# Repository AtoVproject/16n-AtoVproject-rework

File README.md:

<h1>16n AtoVproject Rework</h1>

Product page: https://atovproject.de/products/16nrework

Manual: https://atovproject.de/manuals/16nrework

This is an hardware modified version of the original 16n. https://github.com/16n-faderbank/16n

Fully assembled unit with high end aluminium enclosure, high end faders and set of cables available @ https://schneidersladen.de/de/atovproject-16n-atovproject-rework

Bourns compatible PCBs Panels and cases are available @ https://pushermanproductions.com/product/16n-euro-version-pcb-and-anodized-aluminium-black-panel/

BOM in the PCB folder

Please download the firmware from the original project https://github.com/16n-faderbank/16n/wiki/Firmware:-installation-instructions

<h2>The concept</h2>

The 16n Faderbank is aimed a solving a problem very specific to modular synthesis. As a patch is getting more and more complex a forest of cables has grown over your system before you know it. The 16n allows you to take the control from the modular into a very ergonomic controller that integrates perfectly into a modern studio.

The 16n is a faderbank sending CV, I2C, MIDI jack compatible with all standards, USB MIDI (compatible PC, Mac, iPad etc...) , making it the absolute ultimate controller for any of your hardware and software all in one! 

This unit was redesigned for a DIY workshop organised in the Berlin Modular community. The redesign was done following the wishes and desires of the community. The 16n AtoVproject redesign is the result of this initiative. 

https://www.youtube.com/watch?v=edriUxDgTsg

<h2>Modifications compared to the original are :</h2>

-Updated power section
  Isolated USB power supply. Proper voltage reference. Upgraded filtering.
    This greatly reduce the noise on the outputs. (Measured at less than 6mV)

-Selectable 5v or 10V outputs: Each can be configured to output either 10V or 5V using a dip switch on the back of the module (even when using 5V USB power supply)

-Outputs facing upwards: The outputs will be directly on the front panel reducing the footprint and making outputs much more accessible.

-Eurorack compatible: You would be able to mount the 16n as a 50hp module in your rack and power it from your own power supply. (+12V=42mA, -12V=0mA)

-The footprint of the jack is compatible for banana connectors! So you'll be able to use it with your Serge or Buchla system.

-I2C connector on the PCB to simplify connection to modules like the ER301

-Two versions of the board are available one with high quality ALPS faders and another one with Bourns mid range faders (1/3 of the price of the ALPS).

<h2>Credits</h2>

Based on original open source work by Brian Crabtree, Sean Hellfritsch, Tom Armitage and Brendon Cassidy. Circuit design update by AtoVproject aka Arthur Gibert

As stated by the original designers the original 16n folows a CC-BY-SA licence therefore the 16n AtoVproject is and will always remain entirely open source following the same licence.

If you are making modification to this design, you must correctly credit everyone involved in the initial version, and also share your own changes with the similar license. So you can’t make a fork of 16n or the 16n AtoVproject redesign that you don’t open-source yourself.

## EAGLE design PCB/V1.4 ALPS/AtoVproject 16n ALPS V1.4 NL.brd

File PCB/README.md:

<h1>Gerbers and eagle design files</h1>

Two versions of the board are available. One for high end ALPS faders (which are expensive and quite often out of stock) and another for lower cost Brouns faders (1/3 of the price and more readily available)

The PCB available at https://pushermanproductions.com/product/16n-euro-version-pcb-and-anodized-aluminium-black-panel/ is compatible only with the Brouns faders. 

<h2>Mouser Carts :</h2>

These are complete carts to have all the parts to make the build. They are valid for the latest revision of the boards (v1.4)
Resistors and capacitors are very small so I stronly recommand ordering more (little tip: order resistors and capacitors amounts to the next price break this will make you save a few cents)

Bourns Version
https://www.mouser.com/ProjectManager/ProjectDetail.aspx?AccessID=e279897c7f

ALPS Version
https://www.mouser.com/ProjectManager/ProjectDetail.aspx?AccessID=69297ae739

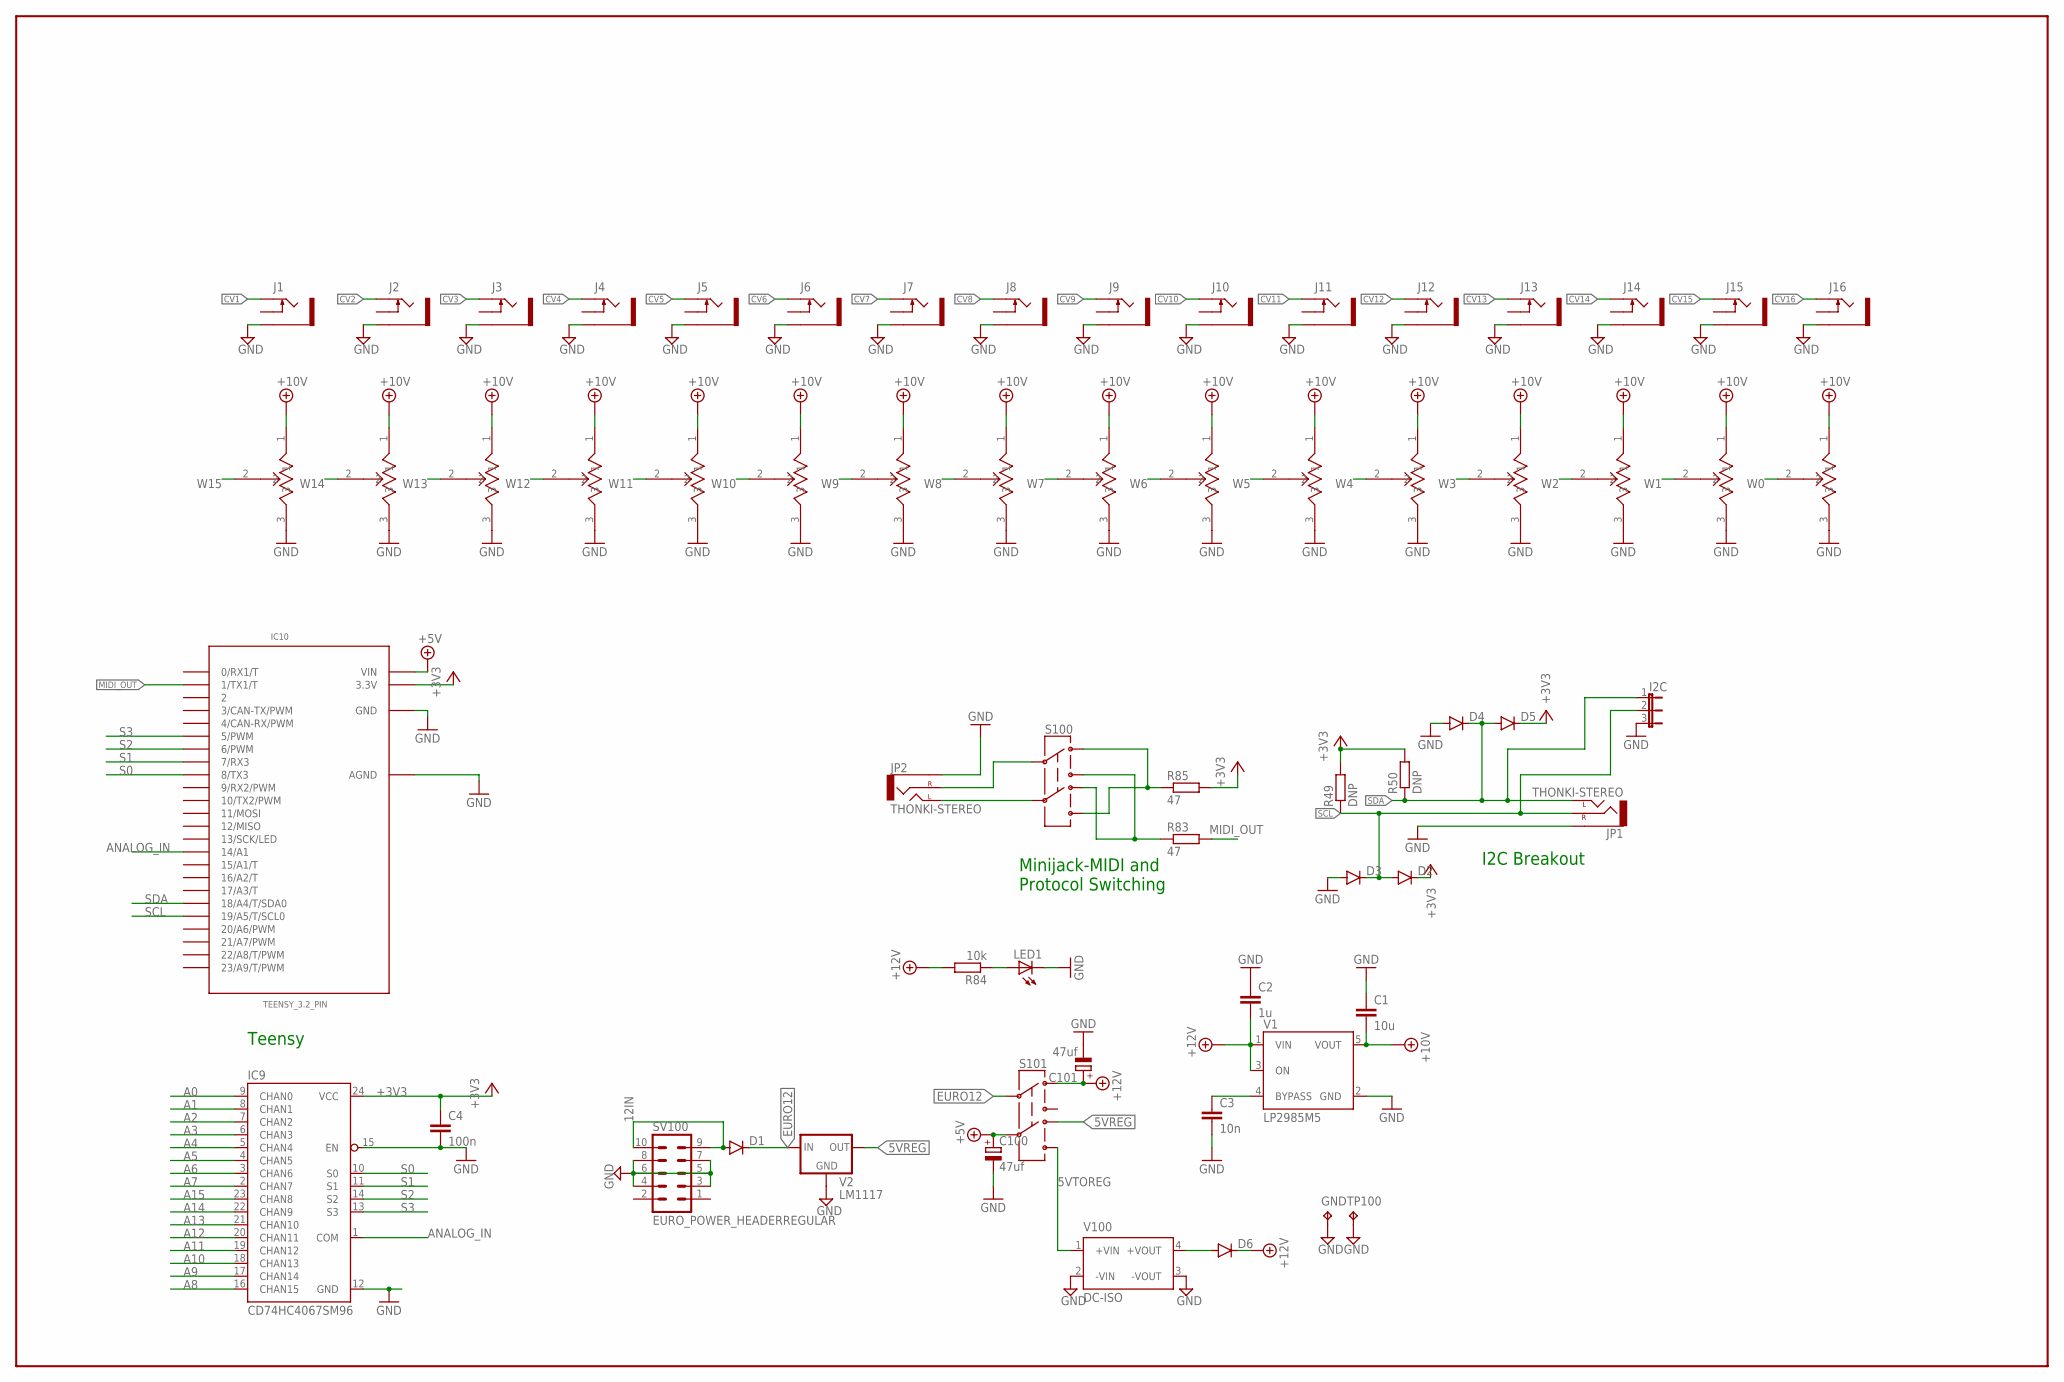
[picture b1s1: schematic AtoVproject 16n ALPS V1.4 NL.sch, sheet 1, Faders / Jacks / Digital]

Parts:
C1: 10u; C0805
C2: 1u; C0805
C3: 10n; C0805
C4: 100n; C0805
C100, C101: 47uf; E2,5-6
D1, D6: DIODE-SOD123; SOD123
D2, D3, D4, D5: DIODESOD123; SOD-123
GND: TPPAD1-17; P1-17
I2C: JP2E; JP2
IC9: CD74HC4067SM96; SOIC127P1030X265-24
IC10: TEENSY_3.2_PIN; TEENSY_3_AND_LC_SERIES_BOARDS_V1.4_TEENSY_3.0-3.2&LC_DIL
J1, J2, J3, J4, J5, J6, J7, J8, J9, J10, J11, J12, J13, J14, J15, J16: THONKICONN; WQP-PJ301M-12JACK-BANANA
JP1, JP2: THONKI-STEREO; WQP-PJ366ST_JACK
LED1: LED; LED3MM
R49, R50: DNP; R0805
R83, R85: 47; R0805
R84: 10k; R0805
S100, S101: SWITCH-DPDTEG2211; EG2211
SV100: EURO_POWER_HEADERREGULAR; EURO_POWER_HEADER
TP100: TPPAD1-17; P1-17
U$1, U$2, U$3, U$4, U$5, U$6, U$7, U$8, U$9, U$10, U$11, U$12, U$13, U$14, U$15, U$16: SLIDERSALPS-60MM; MONOME_RS6011SP600
V1: LP2985M5; SOT23-5
V2: LM1117; SOT223
V100: DC-ISO; TMA

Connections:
5VREG: S101.P2-TA (4), V2.OUT, V2.TAB (OUT)
5VTOREG: S101.P2-TB (6), V100.1 (+VIN)
12IN: D1.A, SV100.9, SV100.10
+3V3: C4.1, D2.C, D5.C, IC9.24 (VCC), IC10.3.3V, R49.2, R50.2, R85.2
+5V: C100.+, IC10.VIN, S101.P2 (5); also elsewhere on the board
+10V: C1.2, U$1.1, U$2.1, U$3.1, U$4.1, U$5.1, U$6.1, U$7.1, U$8.1, U$9.1, U$10.1, U$11.1, U$12.1, U$13.1, U$14.1, U$15.1, U$16.1, V1.5 (VOUT)
+12V: C2.2, C101.+, D6.C, R84.2, S101.P1-TA (1), V1.1 (VIN), V1.3 (ON); also elsewhere on the board
A0: IC9.9 (CHAN0); also elsewhere on the board
A1: IC9.8 (CHAN1); also elsewhere on the board
A2: IC9.7 (CHAN2); also elsewhere on the board
A3: IC9.6 (CHAN3); also elsewhere on the board
A4: IC9.5 (CHAN4); also elsewhere on the board
A5: IC9.4 (CHAN5); also elsewhere on the board
A6: IC9.3 (CHAN6); also elsewhere on the board
A7: IC9.2 (CHAN7); also elsewhere on the board
A8: IC9.16 (CHAN15); also elsewhere on the board
A9: IC9.17 (CHAN14); also elsewhere on the board
A10: IC9.18 (CHAN13); also elsewhere on the board
A11: IC9.19 (CHAN12); also elsewhere on the board
A12: IC9.20 (CHAN11); also elsewhere on the board
A13: IC9.21 (CHAN10); also elsewhere on the board
A14: IC9.22 (CHAN9); also elsewhere on the board
A15: IC9.23 (CHAN8); also elsewhere on the board
ANALOG_IN: IC9.1 (COM), IC10.14/A0 (14/A1)
CV1: J1.P$1_TIP (TIP); also elsewhere on the board
CV2: J2.P$1_TIP (TIP); also elsewhere on the board
CV3: J3.P$1_TIP (TIP); also elsewhere on the board
CV4: J4.P$1_TIP (TIP); also elsewhere on the board
CV5: J5.P$1_TIP (TIP); also elsewhere on the board
CV6: J6.P$1_TIP (TIP); also elsewhere on the board
CV7: J7.P$1_TIP (TIP); also elsewhere on the board
CV8: J8.P$1_TIP (TIP); also elsewhere on the board
CV9: J9.P$1_TIP (TIP); also elsewhere on the board
CV10: J10.P$1_TIP (TIP); also elsewhere on the board
CV11: J11.P$1_TIP (TIP); also elsewhere on the board
CV12: J12.P$1_TIP (TIP); also elsewhere on the board
CV13: J13.P$1_TIP (TIP); also elsewhere on the board
CV14: J14.P$1_TIP (TIP); also elsewhere on the board
CV15: J15.P$1_TIP (TIP); also elsewhere on the board
CV16: J16.P$1_TIP (TIP); also elsewhere on the board
EURO12: D1.C, S101.P1 (2), V2.IN
GND: C1.1, C2.1, C3.2, C4.2, C100.-, C101.-, D3.A, D4.A, GND.TP, I2C.3, IC9.12 (GND), IC9.15 (EN), IC10.AGND, IC10.GND, J1.P$3_SLEEVE (SLEEVE), J2.P$3_SLEEVE (SLEEVE), J3.P$3_SLEEVE (SLEEVE), J4.P$3_SLEEVE (SLEEVE), J5.P$3_SLEEVE (SLEEVE), J6.P$3_SLEEVE (SLEEVE), J7.P$3_SLEEVE (SLEEVE), J8.P$3_SLEEVE (SLEEVE), J9.P$3_SLEEVE (SLEEVE), J10.P$3_SLEEVE (SLEEVE), J11.P$3_SLEEVE (SLEEVE), J12.P$3_SLEEVE (SLEEVE), J13.P$3_SLEEVE (SLEEVE), J14.P$3_SLEEVE (SLEEVE), J15.P$3_SLEEVE (SLEEVE), J16.P$3_SLEEVE (SLEEVE), JP1.P$3_SLEEVE (SLEEVE), JP2.P$3_SLEEVE (SLEEVE), LED1.K (C), SV100.3, SV100.4, SV100.5, SV100.6, SV100.7, SV100.8, TP100.TP, U$1.3, U$2.3, U$3.3, U$4.3, U$5.3, U$6.3, U$7.3, U$8.3, U$9.3, U$10.3, U$11.3, U$12.3, U$13.3, U$14.3, U$15.3, U$16.3, V1.2 (GND), V2.GND, V100.2 (-VIN), V100.3 (-VOUT); also elsewhere on the board
MIDI_OUT: IC10.1 (1/TX1/T), R83.2
unnamed: JP2.P$1_TIP (LEFT), S100.P2 (5)
unnamed: JP2.P$2_SWITCH (RIGHT), S100.P1 (2)
unnamed: R83.1, S100.P1-TB (3), S100.P2-TA (4)
unnamed: R85.1, S100.P1-TA (1), S100.P2-TB (6)
unnamed: LED1.A, R84.1
unnamed: D6.A, V100.4 (+VOUT)
unnamed: C3.1, V1.4 (BYPASS)
S0: IC9.10 (S0), IC10.8 (8/TX3)
S1: IC9.11 (S1), IC10.7 (7/RX3)
S2: IC9.14 (S2), IC10.6 (6/PWM)
S3: IC9.13 (S3), IC10.5 (5/PWM)
SCL: D2.A, D3.C, I2C.2, IC10.19/A5 (19/A5/T/SCL0), JP1.P$2_SWITCH (RIGHT), R49.1
SDA: D4.C, D5.A, I2C.1, IC10.18/A4 (18/A4/T/SDA0), JP1.P$1_TIP (LEFT), R50.1
W0: U$1.2; also elsewhere on the board
W1: U$2.2; also elsewhere on the board
W2: U$3.2; also elsewhere on the board
W3: U$4.2; also elsewhere on the board
W4: U$5.2; also elsewhere on the board
W5: U$6.2; also elsewhere on the board
W6: U$7.2; also elsewhere on the board
W7: U$8.2; also elsewhere on the board
W8: U$9.2; also elsewhere on the board
W9: U$10.2; also elsewhere on the board
W10: U$11.2; also elsewhere on the board
W11: U$12.2; also elsewhere on the board
W12: U$13.2; also elsewhere on the board
W13: U$14.2; also elsewhere on the board
W14: U$15.2; also elsewhere on the board
W15: U$16.2; also elsewhere on the board

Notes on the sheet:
Teensy
I2C Breakout
Minijack-MIDI and Protocol Switching

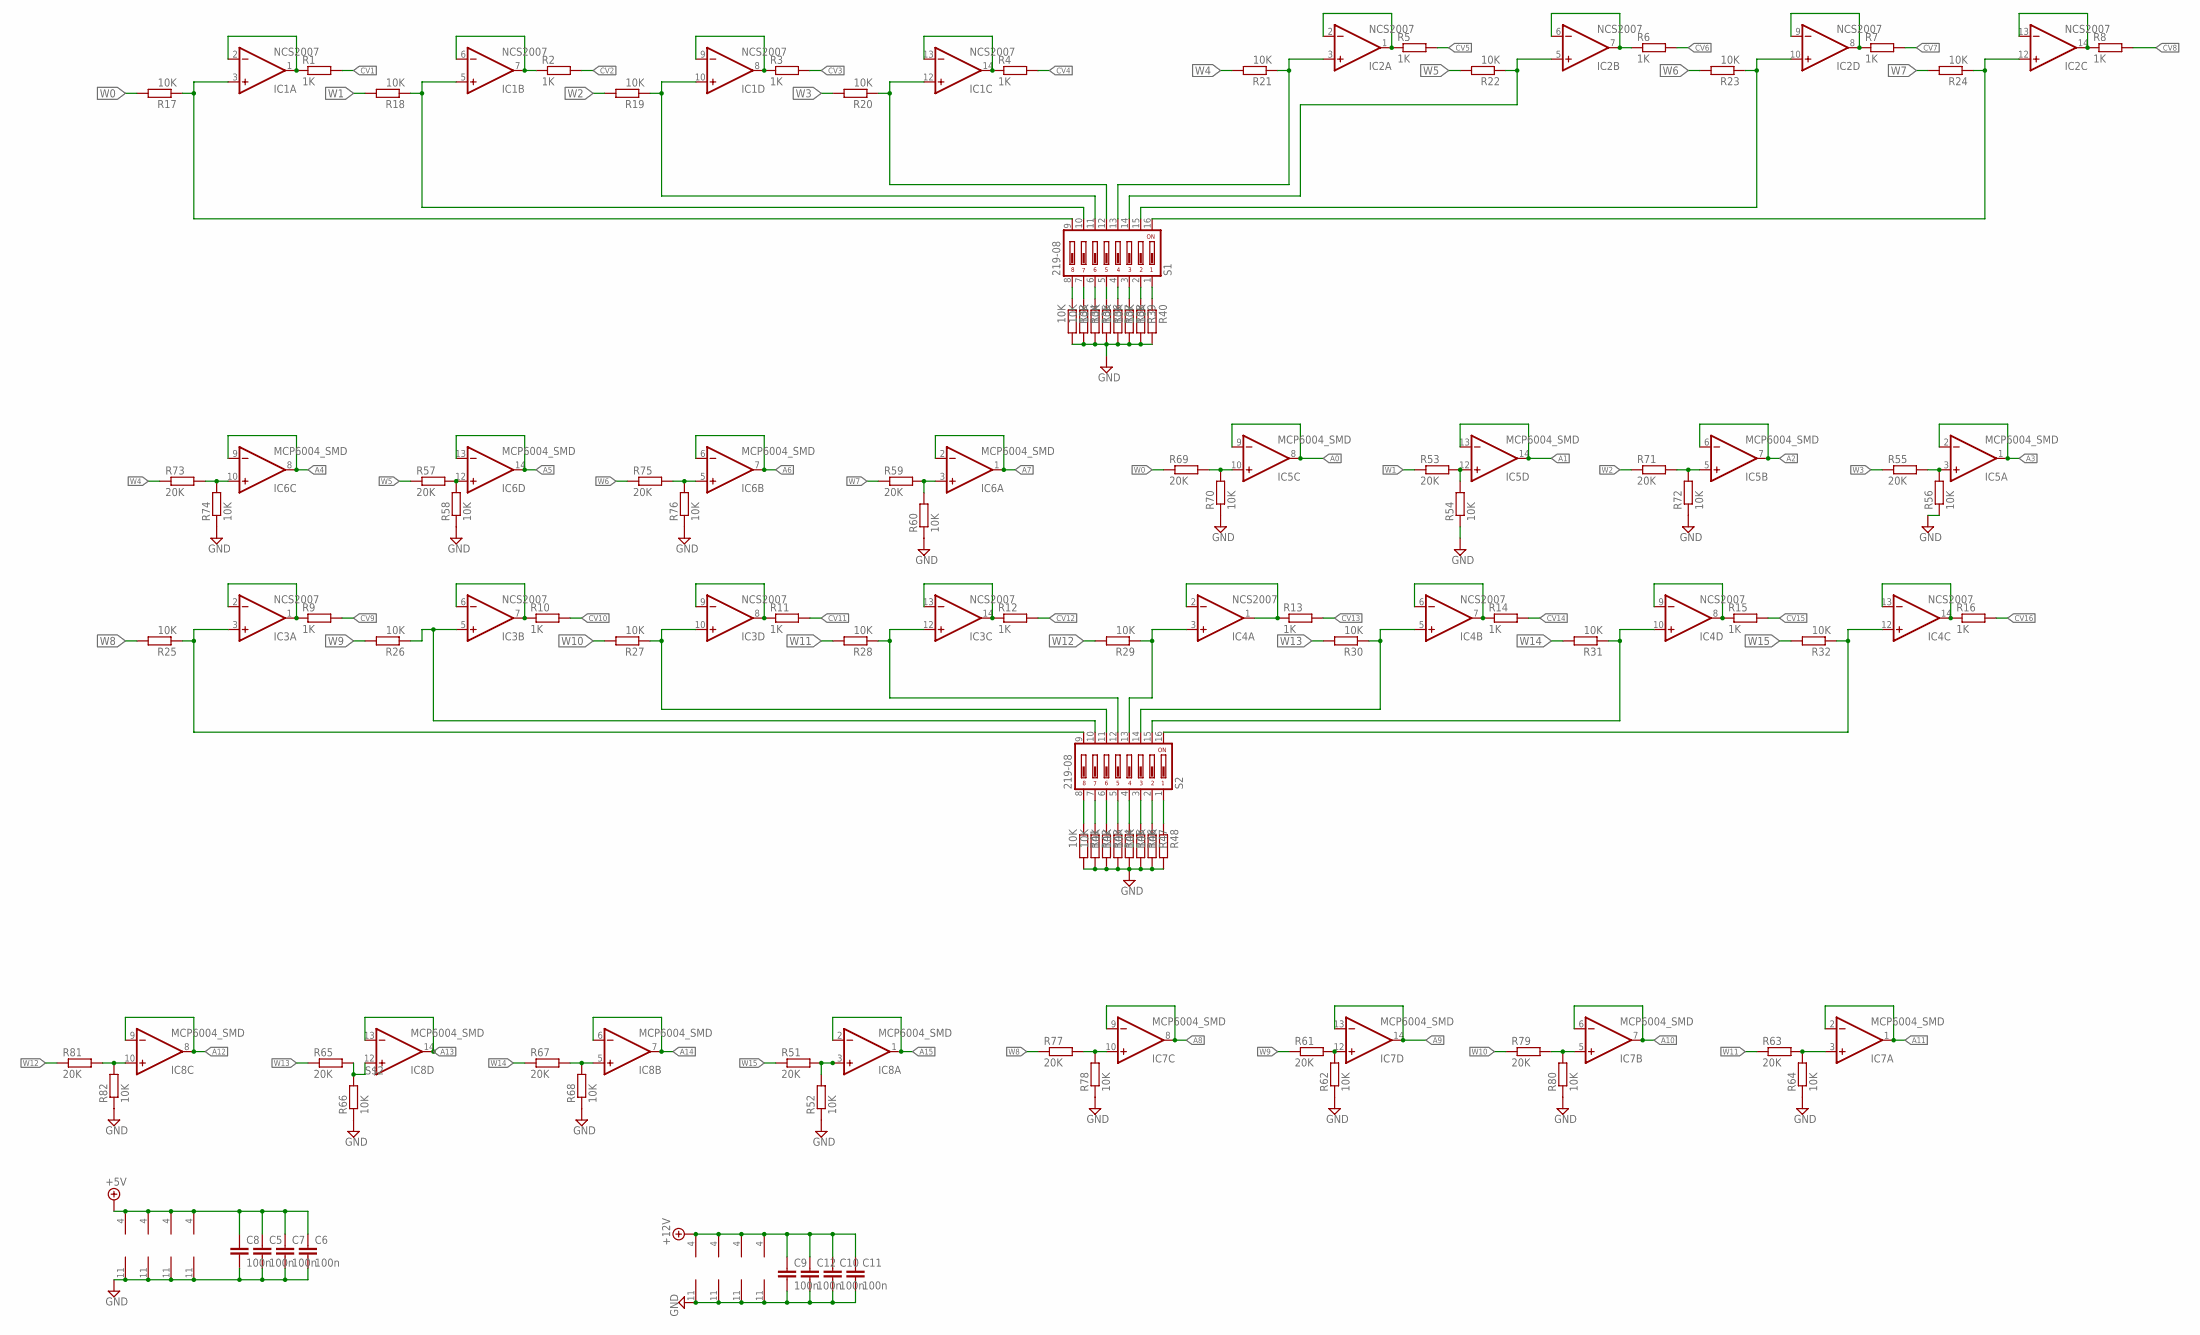
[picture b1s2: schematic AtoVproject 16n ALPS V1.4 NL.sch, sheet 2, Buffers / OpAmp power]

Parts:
C5, C6, C7, C8, C9, C10, C11, C12: 100n; C0805
IC1, IC2, IC3, IC4: NCS2007; SO14
IC5, IC6, IC7, IC8: MCP6004_SMD; SO14
R1, R2, R3, R4, R5, R6, R7, R8, R9, R10, R11, R12, R13, R14, R15, R16: 1K; R0805
R17, R18, R19, R20, R21, R22, R23, R24, R25, R26, R27, R28, R29, R30, R31, R32, R33, R34, R35, R36, R37, R38, R39, R40, R41, R42, R43, R44, R45, R46, R47, R48, R52, R54, R56, R58, R60, R62, R64, R66, R68, R70, R72, R74, R76, R78, R80, R82: 10K; R0805
R51, R53, R55, R57, R59, R61, R63, R65, R67, R69, R71, R73, R75, R77, R79, R81: 20K; R0805
S1, S2: 219-08; CTS-219-08

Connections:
+5V: C5.1, C6.1, C7.1, C8.1, IC5.4 (V+), IC6.4 (V+), IC7.4 (V+), IC8.4 (V+); also elsewhere on the board
+12V: C9.1, C10.1, C11.1, C12.1, IC1.4 (V+), IC2.4 (V+), IC3.4 (V+), IC4.4 (V+); also elsewhere on the board
A0: IC5.8 (OUT), IC5.9 (-IN); also elsewhere on the board
A1: IC5.13 (-IN), IC5.14 (OUT); also elsewhere on the board
A2: IC5.6 (-IN), IC5.7 (OUT); also elsewhere on the board
A3: IC5.1 (OUT), IC5.2 (-IN); also elsewhere on the board
A4: IC6.8 (OUT), IC6.9 (-IN); also elsewhere on the board
A5: IC6.13 (-IN), IC6.14 (OUT); also elsewhere on the board
A6: IC6.6 (-IN), IC6.7 (OUT); also elsewhere on the board
A7: IC6.1 (OUT), IC6.2 (-IN); also elsewhere on the board
A8: IC7.8 (OUT), IC7.9 (-IN); also elsewhere on the board
A9: IC7.13 (-IN), IC7.14 (OUT); also elsewhere on the board
A10: IC7.6 (-IN), IC7.7 (OUT); also elsewhere on the board
A11: IC7.1 (OUT), IC7.2 (-IN); also elsewhere on the board
A12: IC8.8 (OUT), IC8.9 (-IN); also elsewhere on the board
A13: IC8.13 (-IN), IC8.14 (OUT); also elsewhere on the board
A14: IC8.6 (-IN), IC8.7 (OUT); also elsewhere on the board
A15: IC8.1 (OUT), IC8.2 (-IN); also elsewhere on the board
CV1: R1.2; also elsewhere on the board
CV2: R2.2; also elsewhere on the board
CV3: R3.2; also elsewhere on the board
CV4: R4.2; also elsewhere on the board
CV5: R5.2; also elsewhere on the board
CV6: R6.2; also elsewhere on the board
CV7: R7.2; also elsewhere on the board
CV8: R8.2; also elsewhere on the board
CV9: R9.2; also elsewhere on the board
CV10: R10.2; also elsewhere on the board
CV11: R11.2; also elsewhere on the board
CV12: R12.2; also elsewhere on the board
CV13: R13.2; also elsewhere on the board
CV14: R14.2; also elsewhere on the board
CV15: R15.2; also elsewhere on the board
CV16: R16.2; also elsewhere on the board
GND: C5.2, C6.2, C7.2, C8.2, C9.2, C10.2, C11.2, C12.2, IC1.11 (V-), IC2.11 (V-), IC3.11 (V-), IC4.11 (V-), IC5.11 (V-), IC6.11 (V-), IC7.11 (V-), IC8.11 (V-), R33.2, R34.2, R35.2, R36.2, R37.2, R38.2, R39.2, R40.2, R41.2, R42.2, R43.2, R44.2, R45.2, R46.2, R47.2, R48.2, R52.1, R54.1, R56.1, R58.1, R60.1, R62.1, R64.1, R66.1, R68.1, R70.1, R72.1, R74.1, R76.1, R78.1, R80.1, R82.1; also elsewhere on the board
unnamed: IC1.3 (+IN), R17.1, S1.9
unnamed: IC5.5 (+IN), R71.2, R72.2
unnamed: IC5.3 (+IN), R55.2, R56.2
unnamed: R33.1, S1.8
unnamed: IC5.10 (+IN), R69.2, R70.2
unnamed: IC5.12 (+IN), R53.2, R54.2
unnamed: IC1.5 (+IN), R18.1, S1.10
unnamed: IC6.10 (+IN), R73.2, R74.2
unnamed: IC6.12 (+IN), R57.2, R58.2
unnamed: R34.1, S1.7
unnamed: IC6.5 (+IN), R75.2, R76.2
unnamed: IC6.3 (+IN), R59.2, R60.2
unnamed: IC1.10 (+IN), R19.1, S1.11
unnamed: IC7.10 (+IN), R77.2, R78.2
unnamed: IC7.12 (+IN), R61.2, R62.2
unnamed: R35.1, S1.6
unnamed: IC7.5 (+IN), R79.2, R80.2
unnamed: IC7.3 (+IN), R63.2, R64.2
unnamed: IC1.12 (+IN), R20.1, S1.12
unnamed: IC8.3 (+IN), R51.2, R52.2
unnamed: IC8.10 (+IN), R81.2, R82.2
unnamed: R36.1, S1.5
unnamed: IC8.5 (+IN), R67.2, R68.2
unnamed: IC2.3 (+IN), R21.1, S1.13
unnamed: R37.1, S1.4
unnamed: IC2.5 (+IN), R22.1, S1.14
unnamed: R38.1, S1.3
unnamed: IC2.10 (+IN), R23.1, S1.15
unnamed: R39.1, S1.2
unnamed: IC2.12 (+IN), R24.1, S1.16
unnamed: R40.1, S1.1
unnamed: IC3.3 (+IN), R25.1, S2.9
unnamed: R41.1, S2.8
unnamed: IC3.5 (+IN), R26.1, S2.10
unnamed: R42.1, S2.7
unnamed: IC3.10 (+IN), R27.1, S2.11
unnamed: R43.1, S2.6
unnamed: IC3.12 (+IN), R28.1, S2.12
unnamed: R44.1, S2.5
unnamed: IC4.3 (+IN), R29.1, S2.13
unnamed: R45.1, S2.4
unnamed: IC4.5 (+IN), R30.1, S2.14
unnamed: R46.1, S2.3
unnamed: IC4.10 (+IN), R31.1, S2.15
unnamed: R47.1, S2.2
unnamed: IC4.12 (+IN), R32.1, S2.16
unnamed: R48.1, S2.1
unnamed: IC4.8 (OUT), IC4.9 (-IN), R15.1
unnamed: IC1.1 (OUT), IC1.2 (-IN), R1.1
unnamed: IC1.6 (-IN), IC1.7 (OUT), R2.1
unnamed: IC1.8 (OUT), IC1.9 (-IN), R3.1
unnamed: IC1.13 (-IN), IC1.14 (OUT), R4.1
unnamed: IC2.1 (OUT), IC2.2 (-IN), R5.1
unnamed: IC2.6 (-IN), IC2.7 (OUT), R6.1
unnamed: IC2.8 (OUT), IC2.9 (-IN), R7.1
unnamed: IC2.13 (-IN), IC2.14 (OUT), R8.1
unnamed: IC3.1 (OUT), IC3.2 (-IN), R9.1
unnamed: IC3.6 (-IN), IC3.7 (OUT), R10.1
unnamed: IC3.8 (OUT), IC3.9 (-IN), R11.1
unnamed: IC3.13 (-IN), IC3.14 (OUT), R12.1
unnamed: IC4.1 (OUT), IC4.2 (-IN), R13.1
unnamed: IC4.6 (-IN), IC4.7 (OUT), R14.1
unnamed: IC4.13 (-IN), IC4.14 (OUT), R16.1
S$2: IC8.12 (+IN), R65.2, R66.2
W0: R17.2, R69.1; also elsewhere on the board
W1: R18.2, R53.1; also elsewhere on the board
W2: R19.2, R71.1; also elsewhere on the board
W3: R20.2, R55.1; also elsewhere on the board
W4: R21.2, R73.1; also elsewhere on the board
W5: R22.2, R57.1; also elsewhere on the board
W6: R23.2, R75.1; also elsewhere on the board
W7: R24.2, R59.1; also elsewhere on the board
W8: R25.2, R77.1; also elsewhere on the board
W9: R26.2, R61.1; also elsewhere on the board
W10: R27.2, R79.1; also elsewhere on the board
W11: R28.2, R63.1; also elsewhere on the board
W12: R29.2, R81.1; also elsewhere on the board
W13: R30.2, R65.1; also elsewhere on the board
W14: R31.2, R67.1; also elsewhere on the board
W15: R32.2, R51.1; also elsewhere on the board

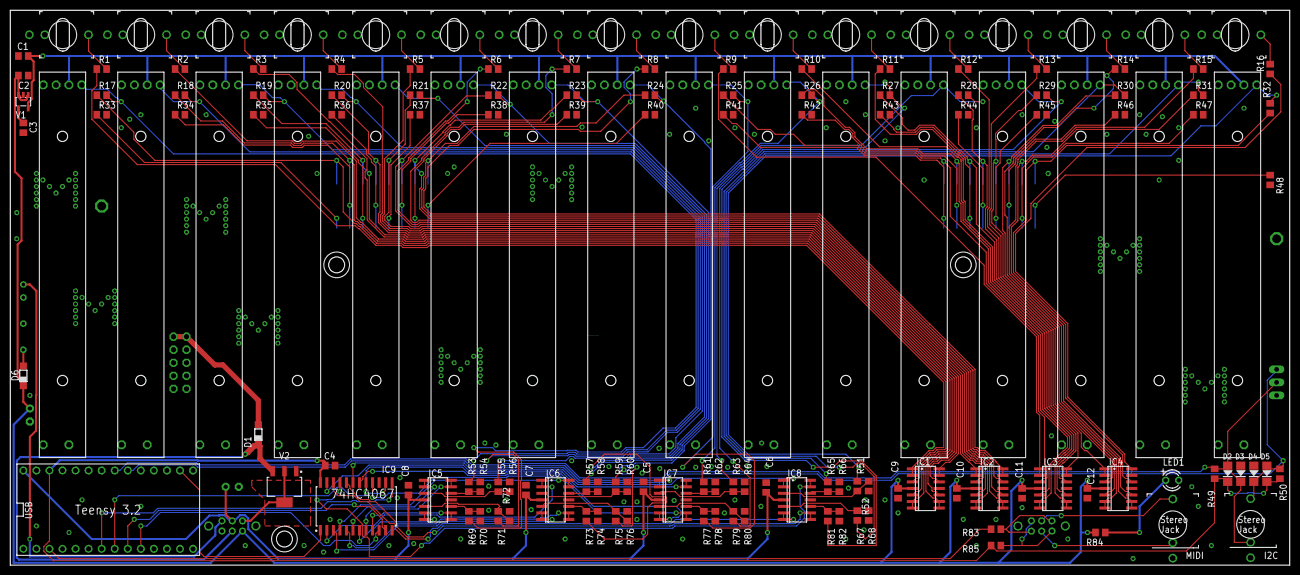
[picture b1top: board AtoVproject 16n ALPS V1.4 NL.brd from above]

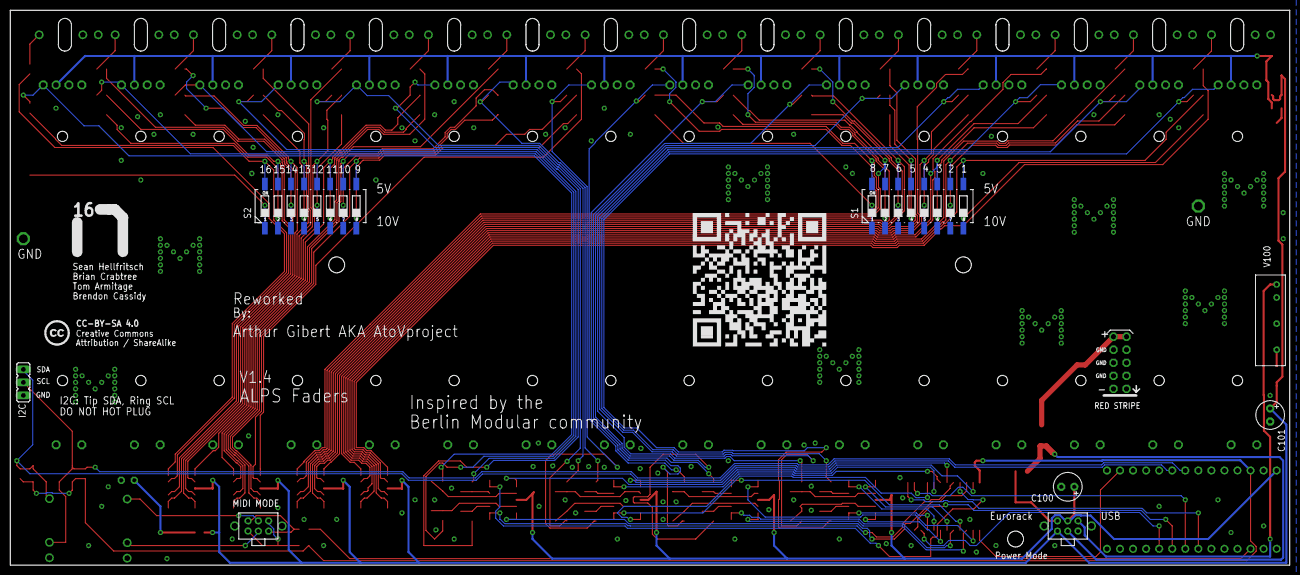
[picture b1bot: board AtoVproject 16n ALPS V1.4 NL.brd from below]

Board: 2 copper layers, 248.9 x 108.0 mm, 161 parts (11 on the bottom side), 136 nets.

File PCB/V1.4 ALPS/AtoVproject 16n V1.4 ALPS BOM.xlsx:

Qty | Value | Device | Package | Parts | Description | Mouser Number | Note
RESISTOR
2 | 47 | R-EU_R0805 | R0805 | R83, R85 | RESISTOR, European symbol | 603-RT0603FRE0747RL
16 | 1K | R-EU_R0805 | R0805 | R1, R2, R3, R4, R5, R6, R7, R8, R9, R10, R11, R12, R13, R14, R15, R16 | RESISTOR, European symbol | 603-RT0603FRE071KL
32 | 10K | R-EU_R0805 | R0805 | R17, R18, R19, R20, R21, R22, R23, R24, R25, R26, R27, R28, R29, R30, R31, R32,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 | RESISTOR, European symbol | 603-RT0603FRE0710KL
16 | 10K* | R-EU_R0805 | R0805 | R33, R34, R35, R36, R37, R38, R39, R40, R41, R42, R43, R44, R45, R46, R47, R48 | RESISTOR, European symbol | 603-RT0603FRE0710KL | Can be changed to modify alternative output (eg 10k => 5V, 1.1k => 1V.) Use his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
1 | 10k | R-EU_R0805 | R0805 | R84 | RESISTOR, European symbol | 603-RT0603FRE0710KL | Modify to change LED brightness
16 | 20K | R-EU_R0805 | R0805 | R51, R53, R55, R57, R59, R61, R63, R65, R67, R69, R71, R73, R75, R77, R79, R81 | RESISTOR, European symbol | 603-RT0603FRE1320KL
2 | DNP | R-EU_R0805 | R0805 | R49, R50 | RESISTOR, European symbol | 603-RT0603FRE074K7L | Has to be changed to 4.7k to use with ER301
16 | SLIDER | SLIDERS | SLIDEPOT-75 | U$1, U$2, U$3, U$4, U$5, U$6, U$7, U$8, U$9, U$10, U$11, U$12, U$13, U$14, U$15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 | ALPS | 688-RS6011SP6003 | tested with 10k-Value shouldn't matter
CAPACITORS
1 | 10n | C-EUC0805 | C0805 | C3 | CAPACITOR, European symbol | 810-CGA3E2X7R1H103K
9 | 100n | C-EUC0805 | C0805 | C4, C5, C6, C7, C8, C9, C10, C11, C12 | CAPACITOR, European symbol | 810-CGA3E2X7R1H104K
1 | 1u | C-EUC0805 | C0805 | C2 | CAPACITOR, European symbol | 810-CGA3E1X7R1C105AC
1 | 10u | C-EUC0805 | C0805 | C1 | CAPACITOR, European symbol | 810-C1608X6S0G106M
2 | 47uf | CPOL-EUE2.5-6 | E2,5-6 | C100, C101 | POLARIZED CAPACITOR, European symbol | 80-ESS476M025AE2EA | Through hole part Use low profile cap
Diodes - Careful these are polarised
2 | 1N5819W-7-F | DIODE-SOD123 | SOD123 | D1, D6 | DIODE | 621-1N5819HW-F | Reverse voltage protection when using Eurorack power
4 | 1N4148W-7-F | DIODESOD123 | SOD-123 | D2, D3, D4, D5 |  | 621-1N4148W-F | Not needed if not using I2C
1 | LED | LED | LED3MM | LED1 |  | 604-WP710A10SRC/E | Indicate power on state
Ics
4 | MCP6004_SMD | MCP6004_SMD | SO14 | IC5, IC6, IC7, IC8 | Generic Quad Op Amp | 579-MCP6004T-I/SL | Has to be rail to rail op amp
4 | NCS2007 | NCS2007 | SO14 | IC1, IC2, IC3, IC4 |  | 863-NCS20074DR2G | Has to be rail to rail op amp
1 | CD74HC4067SM96 | 744067SO24 | SOIC127P1030X265-24 | IC9 | 16-channel analog MUX | 595-CD74HC4067M
Voltage regulators
1 | DC-ISO | DC-ISO | TMA | V100 | DC/DC Converter TME Series 1 Watt | 709-SPU01L-12 | Converts 5V USB to 12V
1 | EURO_POWER_HEADERREGULAR | EURO_POWER_HEADERREGULAR | EURO_POWER_HEADER | SV100 | Power Header
1 | LM1117 | LM1117 5V | SOT223 | V2 | 5V regulator | 926-LM1117IMPX50NOPB
1 | LP2985 | LP2985 10V | SOT23-5 | V1 | 10V regulator | 595-LP2985-10DBVR
Misc
16 | THONKICONN | THONKICONN | WQP-PJ301M-12JACK-BANANA | J1, J2, J3, J4, J5, J6, J7, J8, J9, J10, J11, J12, J13, J14, J15, J16 | 3.5mm socket for Eurorack modular synths |  | Order at Thonk, Modular Addict, Synthcube etc...
2 | THONKI-STEREO | THONKI-STEREO | WQP-PJ366ST_JACK | JP1, JP2 | 3.5mm socket for Eurorack modular synths |  | Order at Thonk, Modular Addict, Synthcube etc...
2 | 8 position DIP switch | 8 position DIP switch | 8 position DIP switch | S1, S2 |  | 774-2198MST
2 |  | SWITCH-DPDTEG2211 | EG2211 | S100, S101 | Switch | 612-EG2211
1 | TEENSY_3.2_PIN | TEENSY_3.2_PIN | TEENSY_3_AND_LC_SERIES_BOARDS_V1.4_TEENSY_3.0-3.2&LC_DIL | IC10 | Teensy 3.1 or 3.2 in a DIL Layout. | 474-DEV-13736
 |  |  |  | Standoff 10mm |  | 710-970100321
 |  |  |  | Standoff 22mm |  | 710-970220361
12 |  |  |  | M3 screw
6 |  |  |  | M3 countersunk screw
1 | 40 pin Headers to cu to size |  |  |  |  | 571-41037410

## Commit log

2019-07-16 Rename panel/Eagle/AtoVproject 16n Panel blank.brd to panel/Eagle/v1.1/AtoVproject 16n Panel blank.brd
2019-07-16 Rename panel/Eagle/v1.1/AtoVproject 16n Panel blank.brd to panel/Eagle/AtoVproject 16n Panel blank.brd
2019-07-16 Rename AtoVproject 16n ALPS V1.2NL.brd to PCB/AtoVproject 16n ALPS V1.2NL.brd
2019-07-16 Rename AtoVproject 16n BOURNS V1.2NL.brd to PCB/AtoVproject 16n BOURNS V1.2NL.brd
2019-07-16 Rename panel/Eagle/AtoVproject 16n Panel blank.brd to panel/AtoVproject 16n Panel blank.brd
2019-07-16 Modified firmware to work with ER301
    -Delay in teensy setup to wait for ER301 to start before initiating i2c conection
    -i2c as master
2019-10-28 typos
2019-12-17 case update
2020-02-03 Change C1 Value in eagle files
2020-02-03 Fix C1 Value in eagle files
2020-02-03 typo fixed, C1 Value Eagle, Add ALPS files
2020-09-03 Removed firmware
2021-07-10 Panel hole fixed
2021-07-10 Case and panel hole fixed

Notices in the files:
PCB/V1.4 ALPS/AtoVproject 16n ALPS V1.4 NL.brd:
CC-BY-SA 4.0
Creative Commons
Attribution / ShareAlike
parts and their libraries:
SparkFun-Electromechanical: Licensing: Creative Commons ShareAlike 4.0 International - https://creativecommons.org/licenses/by-sa/4.0
